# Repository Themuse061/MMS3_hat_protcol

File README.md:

# MMS3 Hat Protocol

## Sekcja 1: Dokumentacja Hat'a

### Krótki opis projektu
Moduł rozszerzeń protokołów komunikacyjnych dla standardu ChainBus. Hat umożliwia podłączanie urządzeń zewnętrznych komunikujących się za pomocą interfejsów UART, RS485, I2C oraz SPI.

Umożliwia  zmianę napięć logicznych (3.3V lub 5V) osobno dla każdej sekcji, a linie komunikacyjne są domyślnie odłączone przy starcie systemu.

### Zgodność ze standardem ChainBus

* ✅  Używa złącza ChainBus, nie zmienia jego miejsca ani pinoutu.
* ✅  Używa wyłącznie interfejsów I2C, SPI lub UART i nie inicjuje samodzielnie nowych transmisji (Nie jest master'em I2C albo SPI).
* ✅  Spełnia wymagania mechaniczne standardu (wymiary PCB, rozstaw otworów).
* ✅  Pobiera maksymalny prąd zgodny z ilością na jednego hat'a
* ✅  Obsługuje napięcie wejściowe BRD_VIN do wartości 48V.

### Komunikacja i adresowanie

#### Adresacja I2C
Do konfiguracji pracy buforów trójstanowych oraz transceiverów RS485 wykorzystywany jest ekspander GPIO.

| Układ (IC)     | Funkcja                              | Adres I2C (7-bit) |
| :------------- | :----------------------------------- | :---------------: |
| **TCA9535PWR** | Ekspander GPIO (sterowanie buforami) | `0100000b` (0x20) |

Uwaga: Adresy expander'a gpio i pamięci EEPROM są zajęte na I2C wychodzącym z hat'a

---

### Konfiguracja i wybór napięć logicznych (3.3V / 5V)

Sekcje UART1, UART2 oraz SPI posiadają niezależną regulację napięcia pracy za pomocą zworek:

| Zworka  | Sekcja | Pozycja 1-2              | Pozycja 2-3            |
| :------ | :----- | :----------------------- | :--------------------- |
| **J8**  | UART 1 | Napięcie logiki **3.3V** | Napięcie logiki **5V** |
| **J14** | UART 2 | Napięcie logiki **3.3V** | Napięcie logiki **5V** |
| **J5**  | SPI    | Napięcie logiki **3.3V** | Napięcie logiki **5V** |

---

### Pełny pinout ekspandera GPIO (TCA9535PWR)

Wszystkie magistrale (z wyjątkiem I2C) są przy starcie urządzenia **fizycznie odłączone**. Do ich aktywacji i konfiguracji służą poniższe piny ekspandera:

| Port    | Nazwa sygnału       | Domyślny stan sprzętowy  | Opis funkcjonalny                                              |
| :------ | :------------------ | :----------------------- | :------------------------------------------------------------- |
| **P00** | `UART 1 OE`         | Niski (L) - Odłączony    | Aktywacja (Output Enable) bufora linii UART 1                  |
| **P01** | `UART 1 RS485 RE_N` | Wysoki (H)  - Wyłączony  | Negowane wejście Receiver Enable ($\overline{RE}$) dla RS485-1 |
| **P02** | `UART 1 SHDN_N`     | Wysoki (H)   - Wyłączony | Negowane wejście Shutdown ($\overline{SD}$) dla RS485-1        |
| **P03** | `UART 1 BONUS OUT`  | Niski (L)                | Dodatkowe wyjście pomocnicze (Bonus Out) na złączu J12         |
| **P04** | `UART 1 BONUS OUT`  | Niski (L)                | Dodatkowe wyjście pomocnicze (Bonus Out) na złączu J12         |
| **P05** | `STATUS LED`        | -                        | Dioda statusowa ogólnego przeznaczenia (LED)                   |
| **P06** | `UART 2 OE`         | Niski (L) - Odłączony    | Aktywacja (Output Enable) bufora linii UART 2                  |
| **P07** | `UART 2 RS485 RE_N` | Wysoki (H) - Wyłączony   | Negowane wejście Receiver Enable ($\overline{RE}$) dla RS485-2 |
| **P10** | `UART 2 SHDN_N`     | Wysoki (H) - Wyłączony   | Negowane wejście Shutdown ($\overline{SD}$) dla RS485-2        |
| **P11** | `UART 2 BONUS OUT`  | Niski (L)                | Dodatkowe wyjście pomocnicze (Bonus Out) na złączu J13         |
| **P12** | `UART 2 BONUS OUT`  | Niski (L)                | Dodatkowe wyjście pomocnicze (Bonus Out) na złączu J13         |
| **P13** | `SPI 1 ENABLE`      | Niski (L) - Odłączony    | Aktywacja (Output Enable) bufora linii SPI                     |
| **P14** | `SPI 1 BONUS IN`    | —                        | Dodatkowe wejście pomocnicze (Bonus In) na złączu J9           |
| **P15** | `SPI 1 BONUS IN`    | —                        | Dodatkowe wejście pomocnicze (Bonus In) na złączu J9           |
| **P16** | `SPI 1 BONUS IN`    | —                        | Dodatkowe wejście pomocnicze (Bonus In) na złączu J9           |
| **P17** | `SPI 1 BONUS OUT`   | —                        | Dodatkowe wyjście pomocnicze (Bonus Out) na złączu J9          |

---

### Konfiguracja trybów pracy: UART vs RS485

Linie komunikacyjne oraz złącza fizyczne są współdzielone pomiędzy standardowym interfejsem UART a różnicowym RS485. Wymaga to odpowiedniej konfiguracji sprzętowej i programowej.

#### Tryb 1: Standardowy UART
Aby używać kanału jako klasycznego interfejsu UART:
1. **Włącz magistralę:** Ustaw odpowiedni pin `UART OE` (P00 lub P06) w stan wysoki (`1`).
2. **Wylutuj rezystor terminujący:** Należy  **odlutować rezystor terminujący RS485** ($120\ \Omega$) przypisany do danego kanału (rezystory są oznaczone  na  PCB). Pozostawienie rezystora obciąży linie RX/TX, co może powodować błędy lub uszkodzenie układu.

#### Tryb 2: Interfejs RS485
Aby używać kanału w standardzie  RS485:
1. **Włącz magistralę:** Ustaw odpowiedni pin `UART OE` (P00 lub P06) w stan wysoki (`1`).
2. **Aktywuj transceiver:** Ustaw piny Receiver Enable (`RE_N`) oraz Shutdown (`SHDN_N`) w stan niski (`0`).
3. **Terminacja linii:** Rezystor terminujący na PCB powinien pozostać wlutowany .

---

### Pinout złączy zewnętrznych

#### J11 (UART1 / RS485-1) oraz J15 (UART2 / RS485-2)
Złącza te współdzielą piny fizyczne dla obu standardów komunikacji.

| Pin   | Nazwa    | Funkcja w trybie UART         | Funkcja w trybie RS485                 |
| :---- | :------- | :---------------------------- | :------------------------------------- |
| **1** | `GND`    | Masa sygnałowa                | Masa odniesienia                       |
| **2** | `V_SEL`  | Wybrane zasilanie (3.3V / 5V) | Wybrane zasilanie (3.3V / 5V)          |
| **3** | `A / RX` | Odbiór danych (RX)            | Linia różnicowa **A** (nieodwracająca) |
| **4** | `B / TX` | Nadawanie danych (TX)         | Linia różnicowa **B** (odwracająca)    |

#### J4 (I2C 3.3V) oraz J6 (I2C 5V)
Złącza magistrali I2C są połączone na stałe do linii ChainBus poprzez odpowiednie translatory poziomów.
* **J4 (3.3V):** Pin 1: GND | Pin 2: 3.3V | Pin 3: SDA 3.3V | Pin 4: SCL 3.3V
* **J6 (5.0V):** Pin 1: GND | Pin 2: 5.0V | Pin 3: SDA 5.0V | Pin 4: SCL 5.0V

#### J7 (SPI)
Złącze magistrali SPI z konwersją napięć (3.3V / 5V w zależności od J5):
* Pin 1: GND | Pin 2: V_SEL | Pin 3: SCK | Pin 4: MOSI | Pin 5: MISO | Pin 6: CS

---

### Złącza pomocnicze (Bonus Pins)

Złącza te służą do wyprowadzenia dodatkowych sygnałów cyfrowych sprzężonych z buforami danej magistrali. Działają tylko wtedy, gdy bufor nadrzędnej magistrali jest włączony (`OE` = `1`).

* **J12 (UART 1):** Pin 1: `P01` (In) | Pin 2: `P02` (Out/In) | Pin 3: `P03` (Out) | Pin 4: `P04` (Out)
* **J13 (UART 2):** Pin 1: `P07` (In) | Pin 2: `P10` (Out/In) | Pin 3: `P11` (Out) | Pin 4: `P12` (Out)
* **J9 (SPI):** Pin 1: `P14` (In) | Pin 2: `P15` (In) | Pin 3: `P16` (In) | Pin 4: `P17` (Out)

---

### Gotowe arkusze hierarchiczne
W projekcie wykorzystano następujące arkusze hierarchiczne:
* **SPI tri state switch** – Moduł przełączania linii interfejsu SPI z użyciem buforów trójstanowych oraz układów konwersji poziomów napięciowych (3.3V <-> 5V).
* **UART tri state switch + RS485 converter** – Blok przełączania linii UART z dopasowaniem poziomów napięć oraz zintegrowanym transceiverem RS485 i układem sterowania przepływem danych (RE/SHDN).

---

## Sekcja 2: Specyfikacja standardu ChainBus

### Architektura i łączenie modułów
Standard ChainBus umożliwia modułowe łączenie hatów. Na jednym MMS3 można zamontować pionowo **do 8 hat'ów**. Połączenie realizowane jest poprzez wpięcie złącza męskiego kolejnego hat'a w złącze żeńskie poprzedniego.

### Komunikacja i sterowanie
Magistrala ChainBus jest w pełni cyfrowa. Płyta główna nie steruje bezpośrednio sygnałami ogólnego przeznaczenia (GPIO) na poszczególnych hat'ach. Wszelkie operacje (np. odczyt czujników, przełączanie magistral) muszą być realizowane przez dedykowane układy scalone komunikujące się przez interfejsy systemowe.

Wybór aktywnego modułu realizowany jest przez układ przełącznika magistrali (bus switch) na płycie głównej. Dzięki temu linie I2C, SPI i UART są niezależne dla każdego hat'a (brak konfliktów adresów I2C między różnymi hatami).
* **Identyfikacja:** Każdy moduł powinien posiadać pamięć EEPROM na magistrali I2C w celu identyfikacji płyty przez system - układ M24C64-W skonfigurowany na adres `1010000` przy liniach adresowych A0, A1, A2 zwartych do masy.

### Zasilanie
Złącze ChainBus dostarcza następujące linie zasilania:

| Magistrala zasilania | Napięcie znamionowe | Maksymalny prąd (łączny dla 8 hatów) | Szacowany prąd na jeden hat |
| :------------------- | :-----------------: | :----------------------------------: | :-------------------------: |
| **5V**               |        5.0 V        |                1.0 A                 |           125 mA            |
| **12V stby**         |       12.0 V        |                0.5 A                 |            65 mA            |
| **BRD_VIN**          |   12.0 V – 48.0 V   |                1.5 A                 |           185 mA            |

*   Komponenty podłączone do linii `BRD_VIN` muszą być przystosowane do pracy z napięciem od 12V do **48 V**.

### Wymagania mechaniczne i złącza
* **Wymiary PCB:** Niedozwolona jest zmiana obrysu płytki oraz położenia otworów montażowych, aby zachować kompatybilność mechaniczną.
* **Pozycjonowanie złączy ChainBus:** Położenie złącza standardu 2x16 SMD (raster 2.54 mm) musi być zgodne z szablonem. Złącze żeńskie montowane jest na stronie FRONT, natomiast złącze męskie na stronie BACK.
* **Komponenty:** Wszystkie komponenty powinny znajdować się na stronie FRONT płytki, aby uniknąć kolizji mechanicznych z elementami sąsiadujących modułów w stosie.

---

## Sekcja 3: Licencje

### Licencje projektu

*   **PCB:** CERN-OHL-P
*   **Software:** MIT License

[Template](https://github.com/KoNaR-Hefajstos/MMS3_hat_templates/) jest na licencji CC0 1.0 Universal. **Reszta projektu nie jest na tej licencji**

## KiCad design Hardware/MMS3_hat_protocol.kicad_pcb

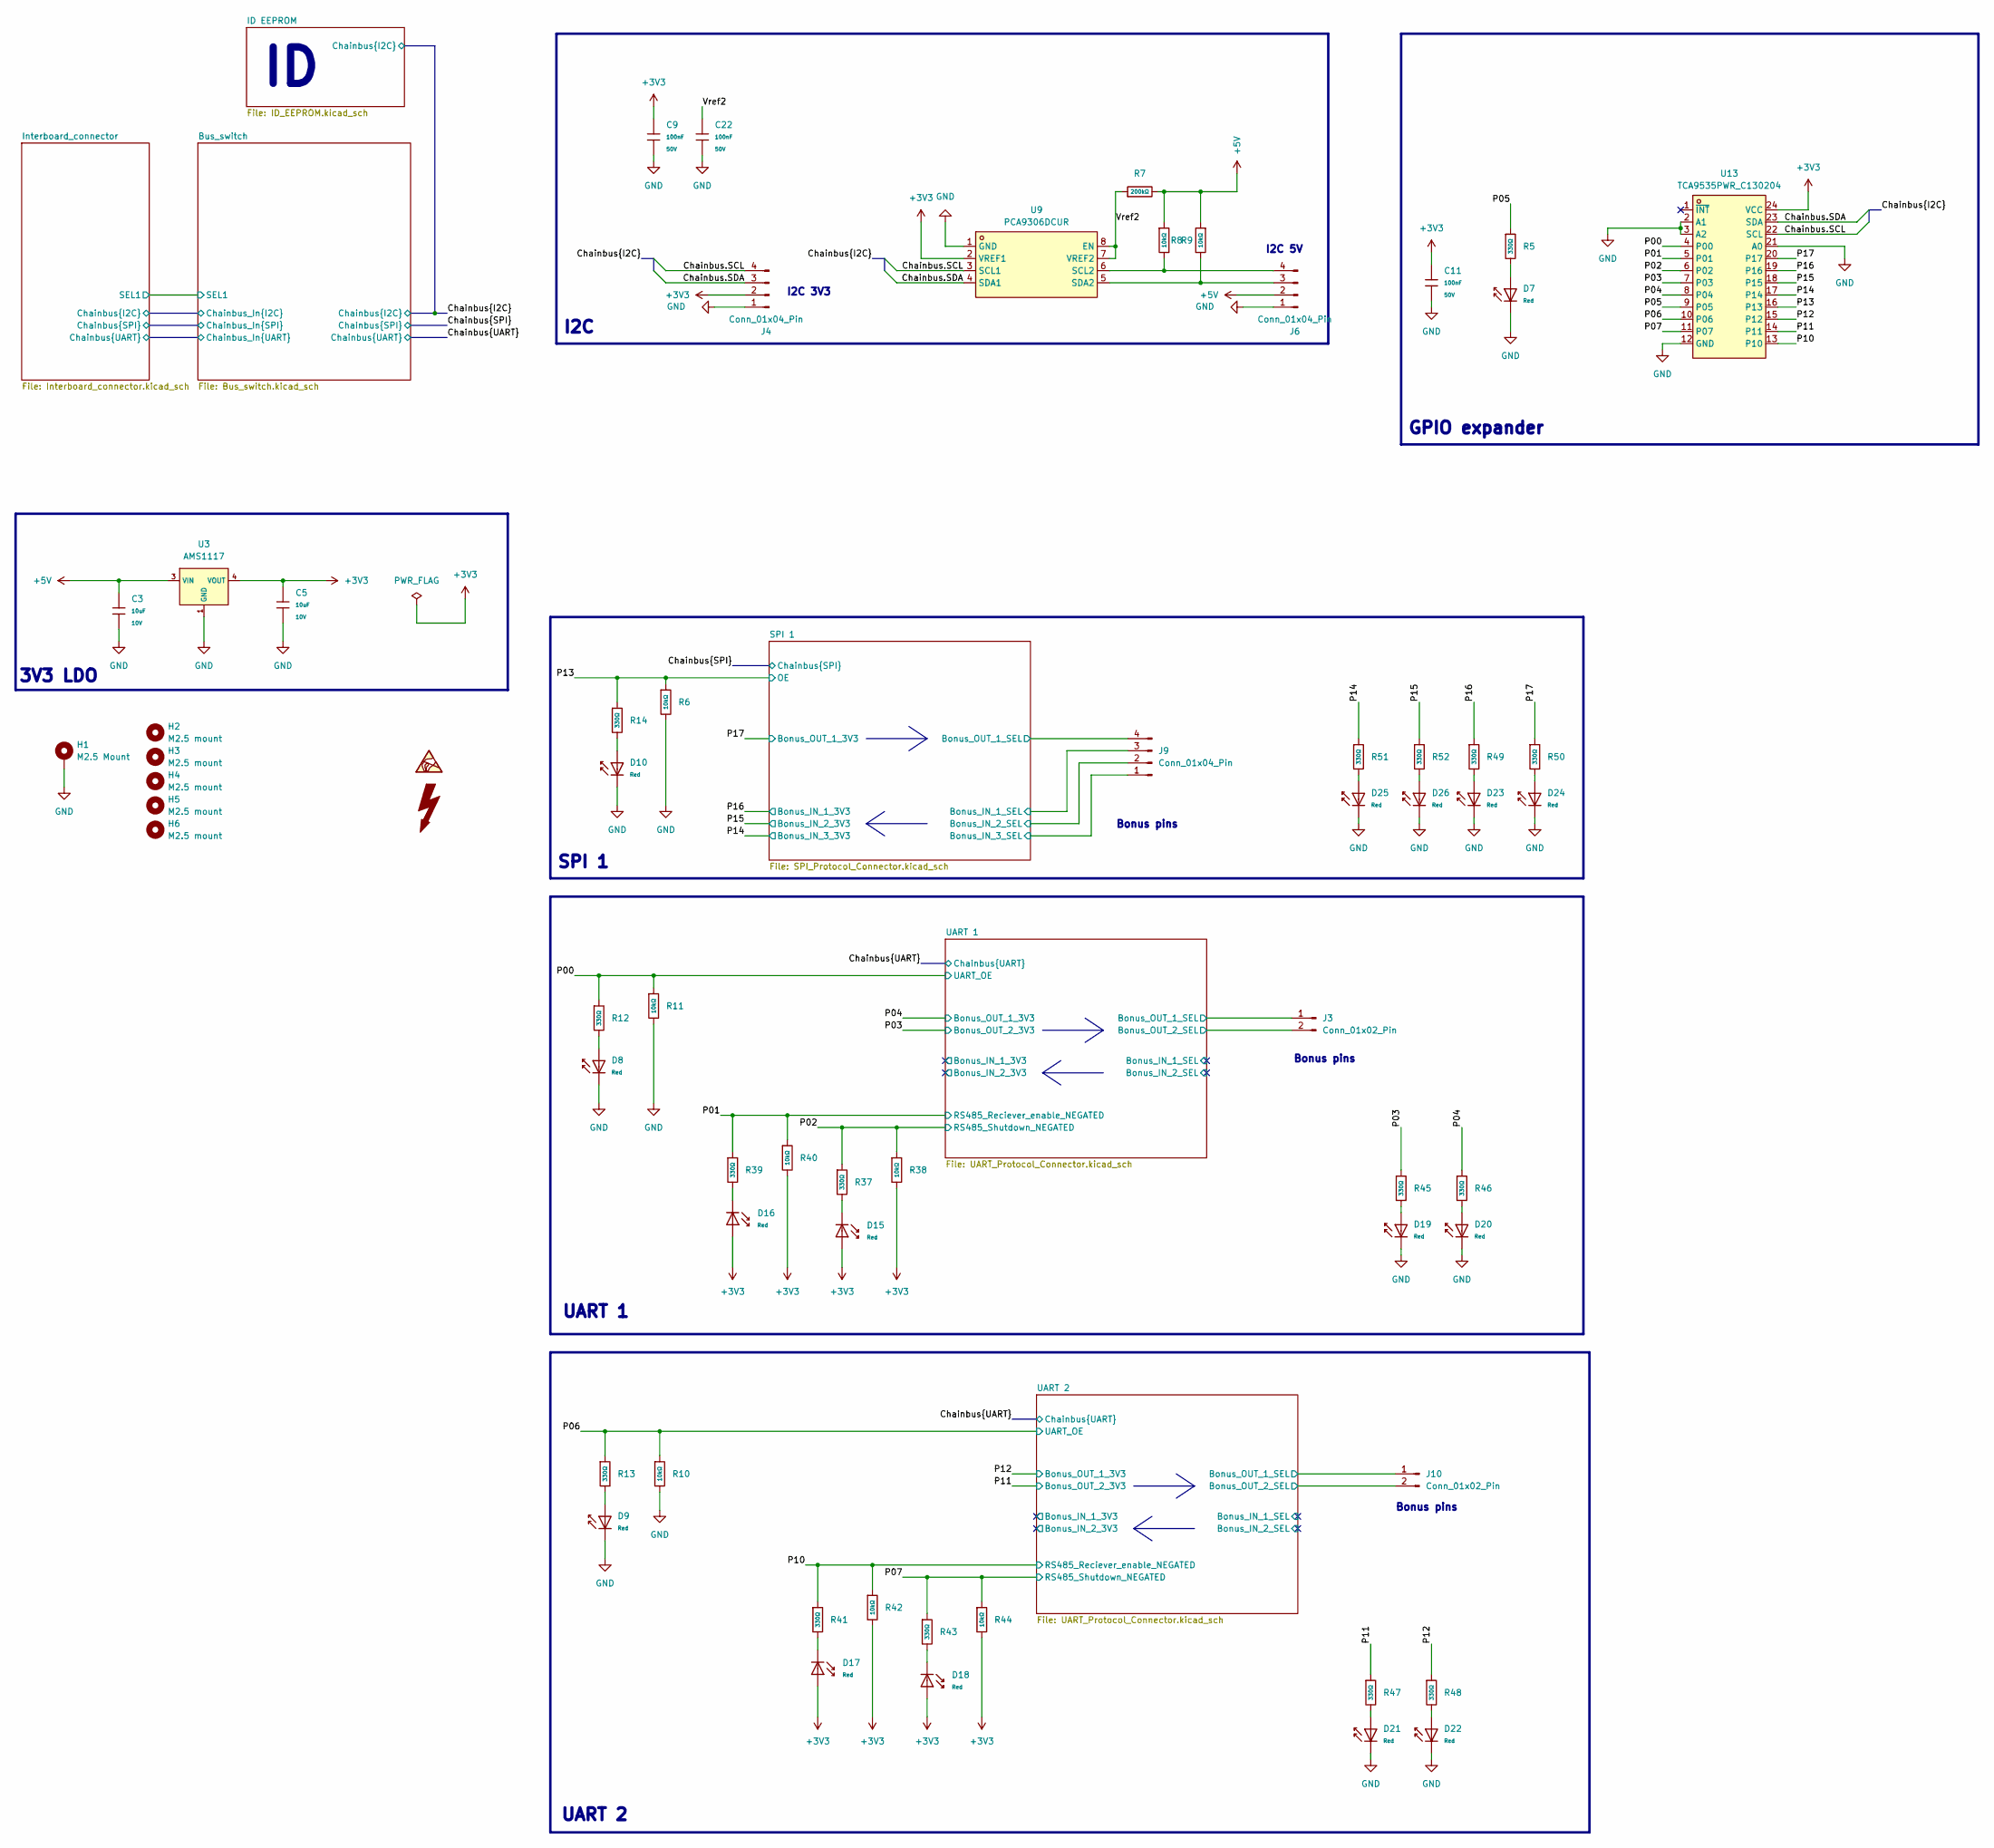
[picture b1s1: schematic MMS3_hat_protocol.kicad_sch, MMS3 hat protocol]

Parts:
C3, C5: 10uF; C_0603; Voltage Rated 10V; Tolerance ±10%; Part CL10A106KP8NNNC; LCSC C19702
C9, C11, C22: 100nF; C_0603; Voltage Rated 50V; Tolerance ±10%; Part CC0603KRX7R9BB104; LCSC C14663
D7, D8, D9, D10, D15, D16, D17, D18, D19, D20, D21, D22, D23, D24, D25, D26: Red; D_0603; Part KT-0603R; LCSC C2286
H1: M2.5 Mount; MountingHole_2.7mm_M2.5_DIN965_Pad_TopOnly
H2, H3, H4, H5, H6: M2.5 mount; MountingHole_2.7mm_M2.5
J3, J10: Conn_01x02_Pin; PinSocket_1x02_P2.54mm_Vertical
J4, J6: Conn_01x04_Pin; JST_XH_S4B-XH-A_1x04_P2.50mm_Horizontal
J9: Conn_01x04_Pin; PinSocket_1x04_P2.54mm_Vertical
R5, R12, R13, R14, R37, R39, R41, R43, R45, R46, R47, R48, R49, R50, R51, R52: 330Ω; R_0402; Overload Voltage (Max) 50V; Tolerance ±1%; Part 0402WGF3300TCE; LCSC C25104
R6, R8, R9, R10, R11, R38, R40, R42, R44: 10kΩ; R_0402; Overload Voltage (Max) 50V; Tolerance ±1%; Part 0402WGF1002TCE; LCSC C25744
R7: 200kΩ; R_0402; Overload Voltage (Max) 50V; Tolerance ±1%; Part 0402WGF2003TCE; LCSC C25764
U3: AMS1117; SOT-223-3_L6.5-W3.4-P2.30-LS7.0-BR; Output Voltage 3.3V; Dropout Voltage 1.3V@(800mA); Part AMS1117-3.3; LCSC C6186
U9: PCA9306DCUR; SSOP-8_L2.0-W2.3-P0.50-LS3.1-BR; MPN PCA9306DCUR; LCSC Part C33196
U13: TCA9535PWR_C130204; TSSOP-24_L7.8-W4.4-P0.65-LS6.4-BL; MPN TCA9535PWR; LCSC Part C130204

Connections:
+3V3: C5.1, C9.1, C11.1, D15.2, D16.2, D17.2, D18.2, J4.2, R38.2, R40.2, R42.2, R44.2, U3.2 (VOUT), U3.4 (VOUT), U9.2 (VREF1), U13.24 (VCC); also elsewhere on the board
+5V: C3.1, J6.2, R7.2, R8.1, R9.1, U3.3 (VIN); also elsewhere on the board
/Chainbus.SCL: J4.4, U9.3 (SCL1), U13.22 (SCL); also elsewhere on the board
/Chainbus.SDA: J4.3, U9.4 (SDA1), U13.23 (SDA); also elsewhere on the board
/P00: R11.1, R12.1, U13.4 (P00); also elsewhere on the board
/P01: R39.1, R40.1, U13.5 (P01); also elsewhere on the board
/P02: R37.1, R38.1, U13.6 (P02); also elsewhere on the board
/P03: R45.1, U13.7 (P03); also elsewhere on the board
/P04: R46.1, U13.8 (P04); also elsewhere on the board
/P05: R5.1, U13.9 (P05)
/P06: R10.1, R13.1, U13.10 (P06); also elsewhere on the board
/P07: R43.1, R44.1, U13.11 (P07); also elsewhere on the board
/P10: R41.1, R42.1, U13.13 (P10); also elsewhere on the board
/P11: R47.1, U13.14 (P11); also elsewhere on the board
/P12: R48.1, U13.15 (P12); also elsewhere on the board
/P13: R6.1, R14.1, U13.16 (P13); also elsewhere on the board
/P14: R51.1, U13.17 (P14); also elsewhere on the board
/P15: R52.1, U13.18 (P15); also elsewhere on the board
/P16: R49.1, U13.19 (P16); also elsewhere on the board
/P17: R50.1, U13.20 (P17); also elsewhere on the board
/SPI 1/Bonus_IN_1_SEL: J9.3; also elsewhere on the board
/SPI 1/Bonus_IN_2_SEL: J9.2; also elsewhere on the board
/SPI 1/Bonus_IN_3_SEL: J9.1; also elsewhere on the board
/SPI 1/Bonus_OUT_1_SEL: J9.4; also elsewhere on the board
/UART 1/Bonus_OUT_1_SEL: J3.1; also elsewhere on the board
/UART 1/Bonus_OUT_2_SEL: J3.2; also elsewhere on the board
/UART 2/Bonus_OUT_1_SEL: J10.1; also elsewhere on the board
/UART 2/Bonus_OUT_2_SEL: J10.2; also elsewhere on the board
/Vref2: C22.1, R7.1, U9.7 (VREF2), U9.8 (EN)
GND: C3.2, C5.2, C9.2, C11.2, C22.2, D7.1, D8.1, D9.1, D10.1, D19.1, D20.1, D21.1, D22.1, D23.1, D24.1, D25.1, D26.1, H1.1 (1_1), J4.1, J6.1, R6.2, R10.2, R11.2, U3.1 (GND), U9.1 (GND), U13.2 (A1), U13.3 (A2), U13.12 (GND), U13.21 (A0); also elsewhere on the board
unnamed: D7.2, R5.2
unnamed: D8.2, R12.2
unnamed: D9.2, R13.2
unnamed: D10.2, R14.2
unnamed: D15.1, R37.2
unnamed: D16.1, R39.2
unnamed: D17.1, R41.2
unnamed: D18.1, R43.2
unnamed: D19.2, R45.2
unnamed: D20.2, R46.2
unnamed: D21.2, R47.2
unnamed: D22.2, R48.2
unnamed: D23.2, R49.2
unnamed: D24.2, R50.2
unnamed: D25.2, R51.2
unnamed: D26.2, R52.2
unnamed: J6.3, R9.2, U9.5 (SDA2)
unnamed: J6.4, R8.2, U9.6 (SCL2)

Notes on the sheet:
I2C 3V3
GPIO expander
Bonus pins
UART 1
I2C 5V
3V3 LDO
I2C
SPI 1
UART 2

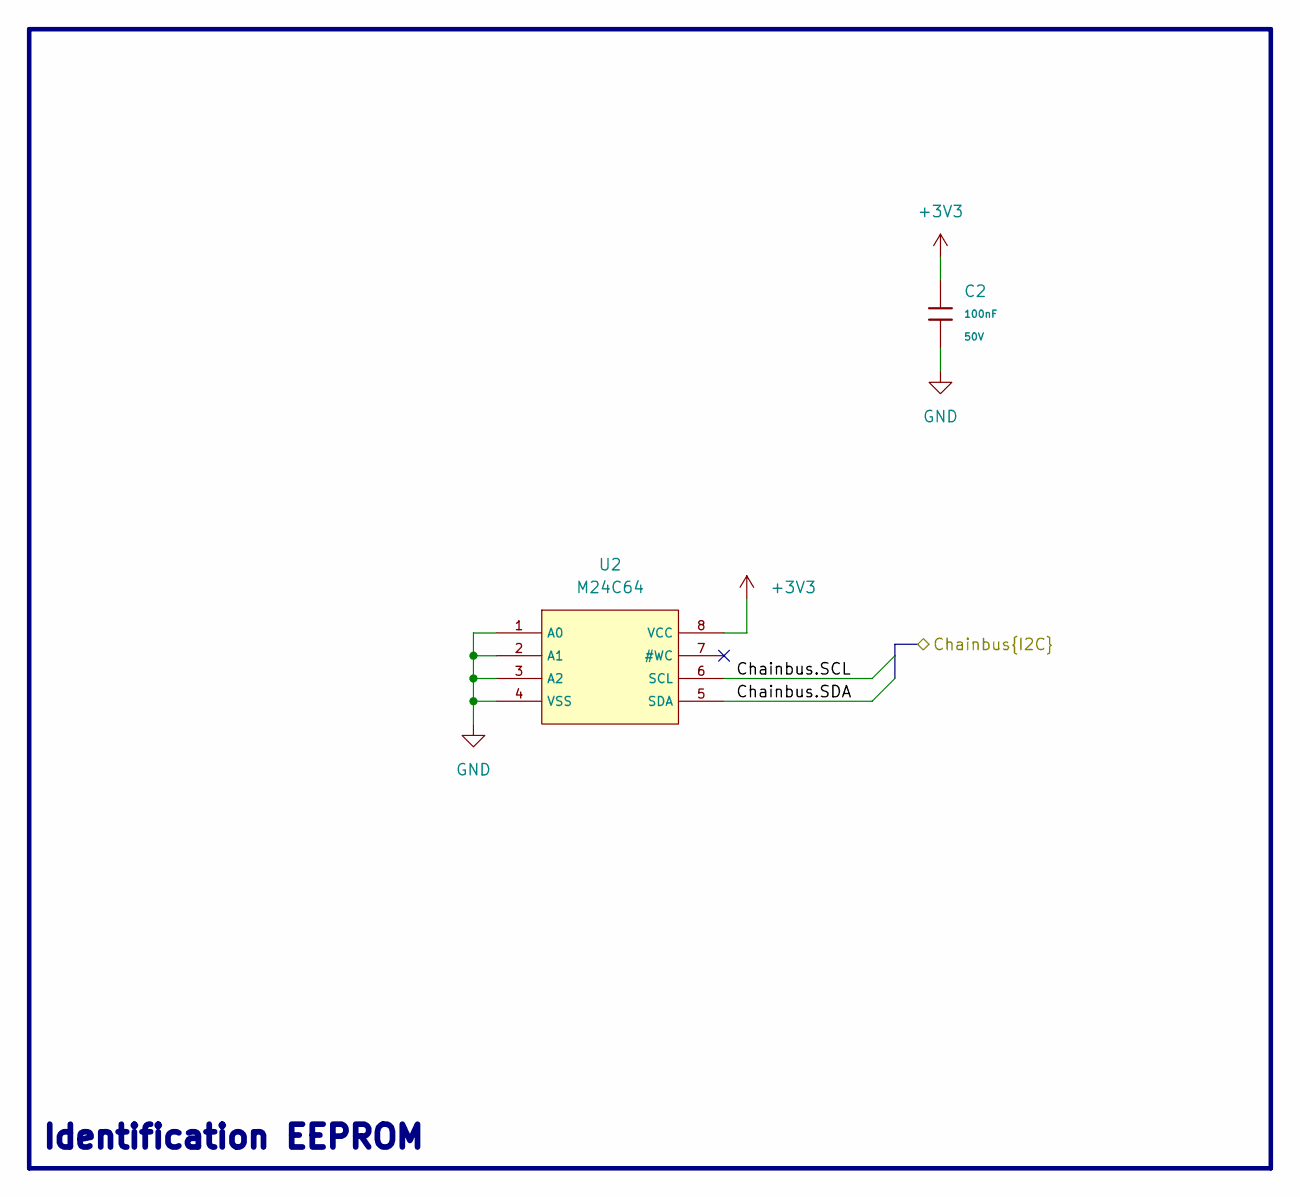
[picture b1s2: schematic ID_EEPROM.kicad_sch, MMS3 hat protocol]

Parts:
C2: 100nF; C_0603; Voltage Rated 50V; Tolerance ±10%; Part CC0603KRX7R9BB104; LCSC C14663
U2: M24C64; SOIC-8_L5.0-W4.0-P1.27-LS6.0-BL; Supply Voltage 1.8V~5.5V; Part M24C64-RMN6TP; LCSC C79988

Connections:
+3V3: C2.1, U2.8 (VCC); also elsewhere on the board
/Chainbus.SCL: U2.6 (SCL); also elsewhere on the board
/Chainbus.SDA: U2.5 (SDA); also elsewhere on the board
GND: C2.2, U2.1 (A0), U2.2 (A1), U2.3 (A2), U2.4 (VSS); also elsewhere on the board

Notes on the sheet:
Identification EEPROM

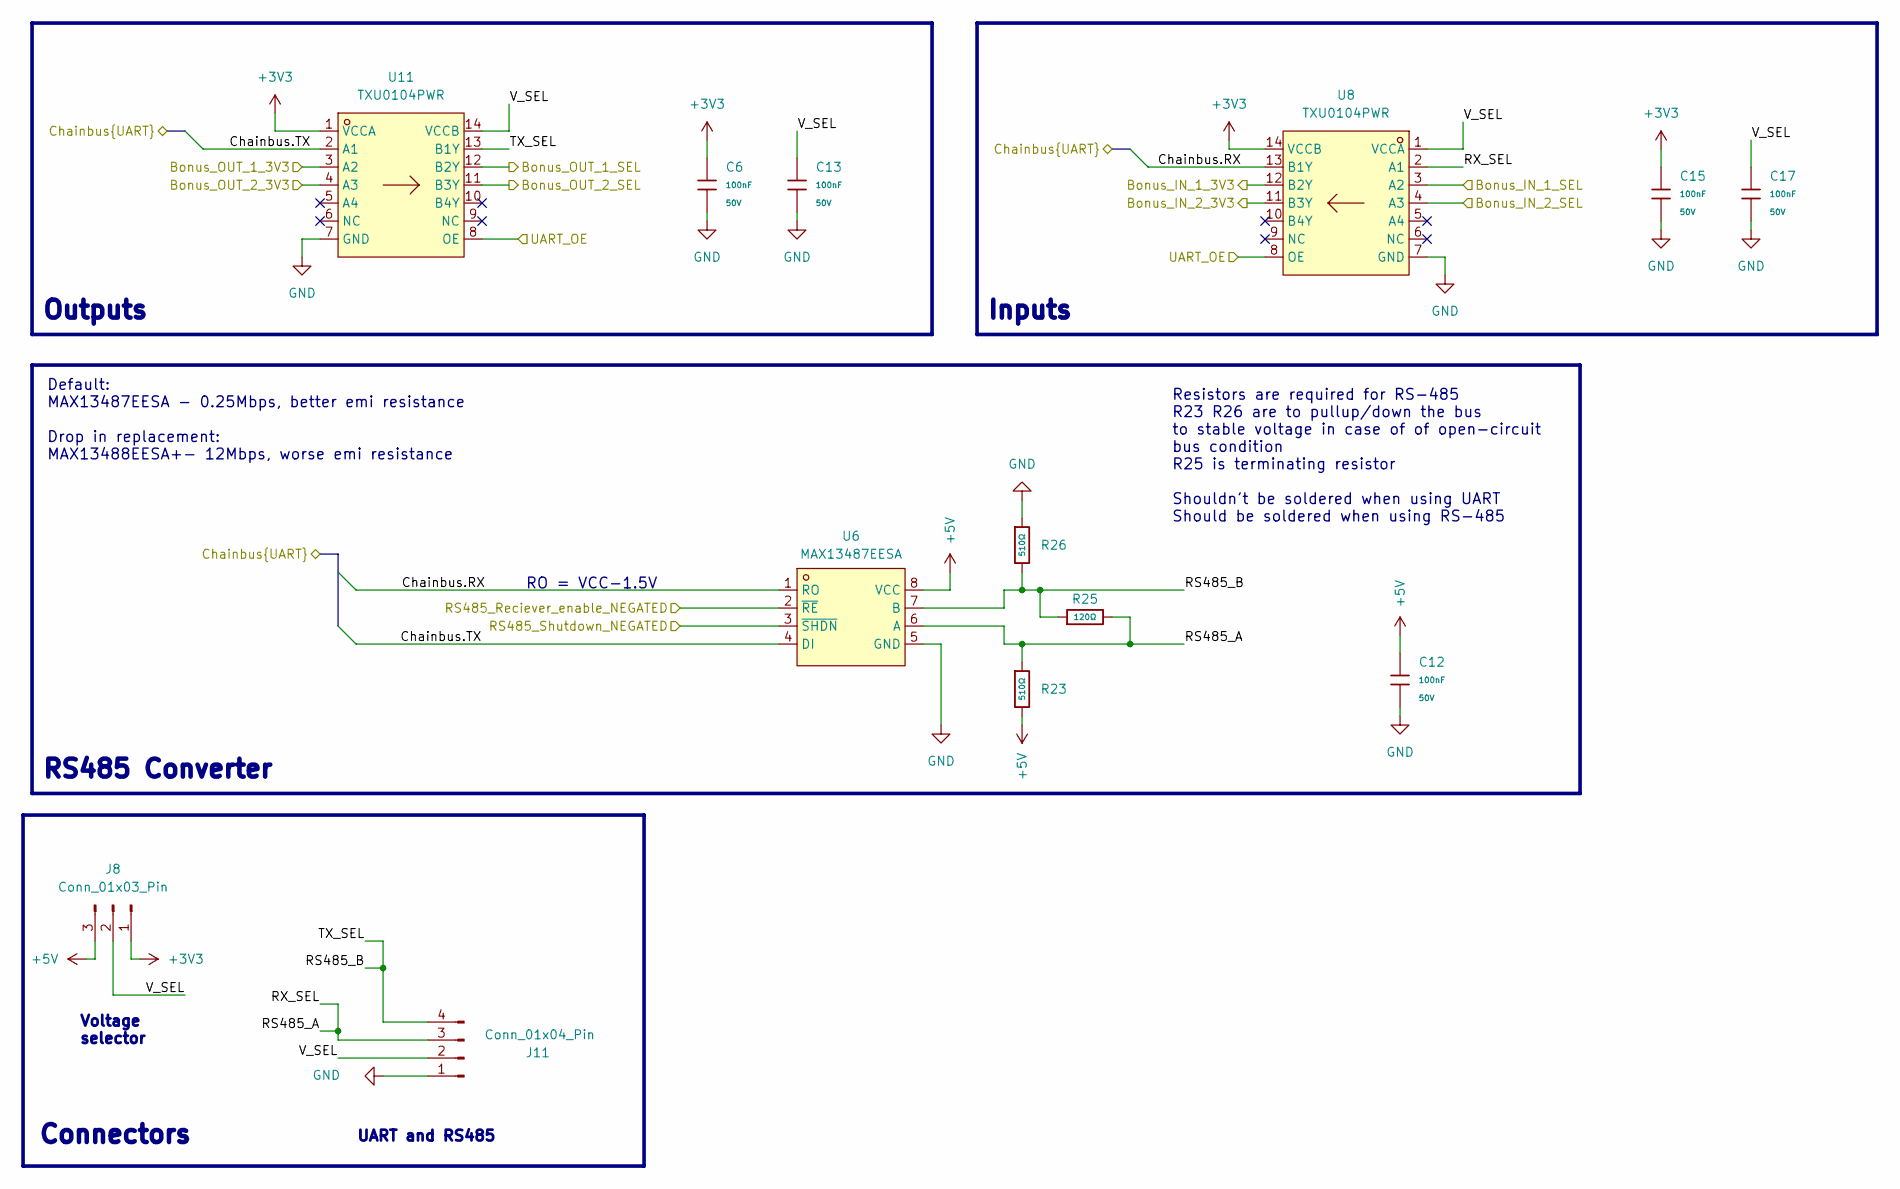
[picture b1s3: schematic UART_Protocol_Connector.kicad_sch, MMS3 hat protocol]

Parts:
C6, C12, C13, C15, C17: 100nF; C_0603; Voltage Rated 50V; Tolerance ±10%; Part CC0603KRX7R9BB104; LCSC C14663
J8: Conn_01x03_Pin; PinSocket_1x03_P2.54mm_Horizontal
J11: Conn_01x04_Pin; JST_XH_S4B-XH-A_1x04_P2.50mm_Horizontal
R23, R26: 510Ω; R_0603; Overload Voltage (Max) 75V; Tolerance ±1%; Part 0603WAF5100T5E; LCSC C23193
R25: 120Ω; R_0603; Overload Voltage (Max) 75V; Tolerance ±1%; Part 0603WAF1200T5E; LCSC C22787
U6: MAX13487EESA; SOIC-8_L4.9-W3.9-P1.27-LS6.0-BL; MPN MAX13487EESA+T; LCSC Part C18347
U8, U11: TXU0104PWR; TSSOP-14_L5.0-W4.4-P0.65-LS6.4-BL; LCSC Part C2938871

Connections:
+3V3: C6.1, C15.1, J8.1, U8.14 (VCCB), U11.1 (VCCA); also elsewhere on the board
+5V: C12.1, J8.3, R23.2, U6.8 (VCC); also elsewhere on the board
/Chainbus.RX: U6.1 (RO), U8.13 (B1Y); also elsewhere on the board
/Chainbus.TX: U6.4 (DI), U11.2 (A1); also elsewhere on the board
/P00: U8.8 (OE), U11.8 (OE); also elsewhere on the board
/P01: U6.2 (~RE); also elsewhere on the board
/P02: U6.3 (~SHDN); also elsewhere on the board
/P03: U11.4 (A3); also elsewhere on the board
/P04: U11.3 (A2); also elsewhere on the board
/UART 1/Bonus_IN_1_3V3: U8.12 (B2Y)
/UART 1/Bonus_IN_1_SEL: U8.3 (A2)
/UART 1/Bonus_IN_2_3V3: U8.11 (B3Y)
/UART 1/Bonus_IN_2_SEL: U8.4 (A3)
/UART 1/Bonus_OUT_1_SEL: U11.12 (B2Y); also elsewhere on the board
/UART 1/Bonus_OUT_2_SEL: U11.11 (B3Y); also elsewhere on the board
/UART 1/RS485_A: J11.3, R23.1, R25.2, U6.6 (A), U8.2 (A1)
/UART 1/RS485_B: J11.4, R25.1, R26.2, U6.7 (B), U11.13 (B1Y)
/UART 1/V_SEL: C13.1, C17.1, J8.2, J11.2, U8.1 (VCCA), U11.14 (VCCB)
GND: C6.2, C12.2, C13.2, C15.2, C17.2, J11.1, R26.1, U6.5 (GND), U8.7 (GND), U11.7 (GND); also elsewhere on the board

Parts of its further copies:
C14, C18, C19, C20, C21: 100nF; C_0603; Voltage Rated 50V; Tolerance ±10%; Part CC0603KRX7R9BB104; LCSC C14663
J14: Conn_01x03_Pin; PinSocket_1x03_P2.54mm_Horizontal
J15: Conn_01x04_Pin; JST_XH_S4B-XH-A_1x04_P2.50mm_Horizontal
R24, R27: 510Ω; R_0603; Overload Voltage (Max) 75V; Tolerance ±1%; Part 0603WAF5100T5E; LCSC C23193
R28: 120Ω; R_0603; Overload Voltage (Max) 75V; Tolerance ±1%; Part 0603WAF1200T5E; LCSC C22787
U10, U12: TXU0104PWR; TSSOP-14_L5.0-W4.4-P0.65-LS6.4-BL; LCSC Part C2938871
U15: MAX13487EESA; SOIC-8_L4.9-W3.9-P1.27-LS6.0-BL; MPN MAX13487EESA+T; LCSC Part C18347

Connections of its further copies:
+3V3: C18.1, C20.1, J14.1, U10.1 (VCCA), U12.14 (VCCB); also elsewhere on the board
+5V: C14.1, J14.3, R24.2, U15.8 (VCC); also elsewhere on the board
/Chainbus.RX: U12.13 (B1Y), U15.1 (RO); also elsewhere on the board
/Chainbus.TX: U10.2 (A1), U15.4 (DI); also elsewhere on the board
/P06: U10.8 (OE), U12.8 (OE); also elsewhere on the board
/P07: U15.3 (~SHDN); also elsewhere on the board
/P10: U15.2 (~RE); also elsewhere on the board
/P11: U10.4 (A3); also elsewhere on the board
/P12: U10.3 (A2); also elsewhere on the board
/UART 2/Bonus_IN_1_3V3: U12.12 (B2Y)
/UART 2/Bonus_IN_1_SEL: U12.3 (A2)
/UART 2/Bonus_IN_2_3V3: U12.11 (B3Y)
/UART 2/Bonus_IN_2_SEL: U12.4 (A3)
/UART 2/Bonus_OUT_1_SEL: U10.12 (B2Y); also elsewhere on the board
/UART 2/Bonus_OUT_2_SEL: U10.11 (B3Y); also elsewhere on the board
/UART 2/RS485_A: J15.3, R24.1, R28.2, U12.2 (A1), U15.6 (A)
/UART 2/RS485_B: J15.4, R27.2, R28.1, U10.13 (B1Y), U15.7 (B)
/UART 2/V_SEL: C19.1, C21.1, J14.2, J15.2, U10.14 (VCCB), U12.1 (VCCA)
GND: C14.2, C18.2, C19.2, C20.2, C21.2, J15.1, R27.1, U10.7 (GND), U12.7 (GND), U15.5 (GND); also elsewhere on the board

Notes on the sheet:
Connectors
Voltage selector
UART and RS485
Default: MAX13487EESA - 0.25Mbps, better emi resistance Drop in replacement: MAX13488EESA+- 12Mbps, worse emi resistance
Inputs
RO = VCC-1.5V
Resistors are required for RS-485 R23 R26 are to pullup/down the bus to stable voltage in case of of open-circuit bus condition R25 is terminating resistor Shouldn't be soldered when using UART Should be soldered when using RS-485
RS485 Converter
Outputs

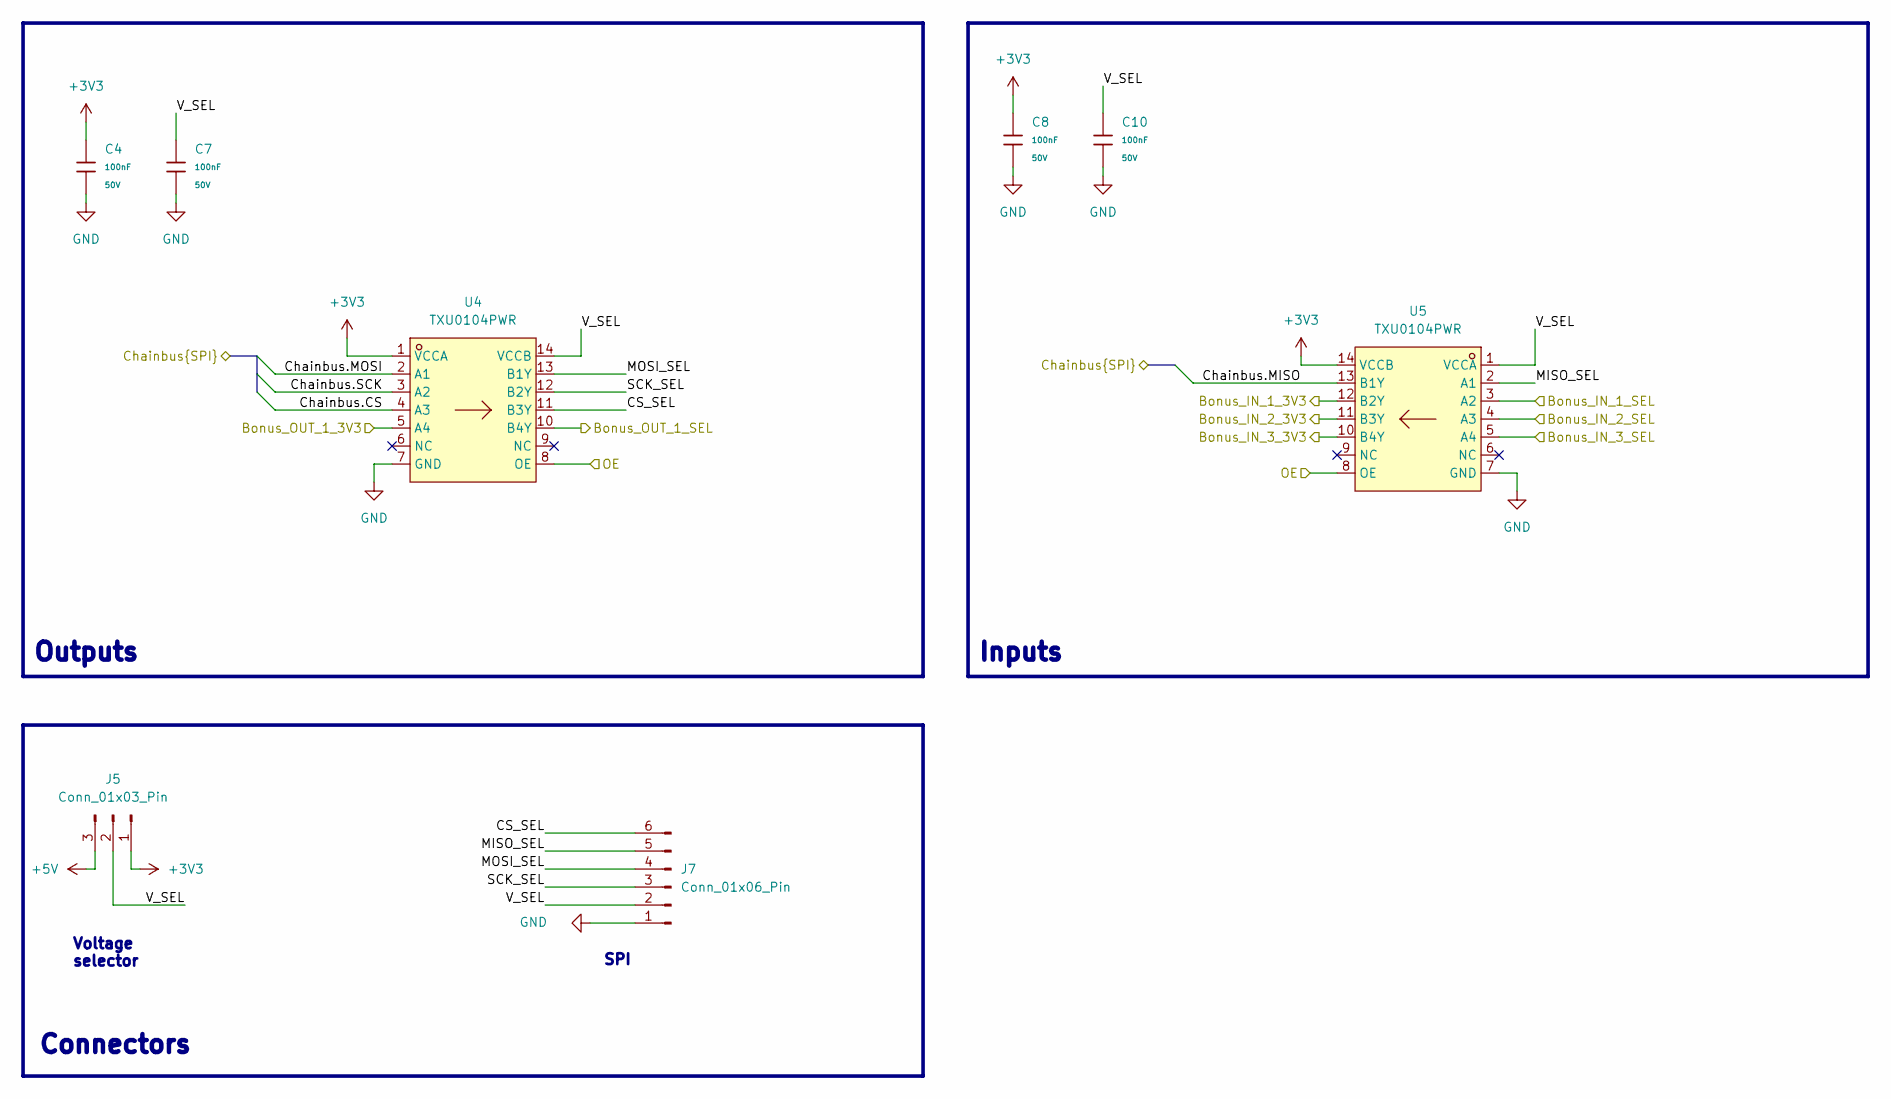
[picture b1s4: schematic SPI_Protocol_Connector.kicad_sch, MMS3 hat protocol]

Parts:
C4, C7, C8, C10: 100nF; C_0603; Voltage Rated 50V; Tolerance ±10%; Part CC0603KRX7R9BB104; LCSC C14663
J5: Conn_01x03_Pin; PinSocket_1x03_P2.54mm_Horizontal
J7: Conn_01x06_Pin; JST_XH_S6B-XH-A_1x06_P2.50mm_Horizontal
U4, U5: TXU0104PWR; TSSOP-14_L5.0-W4.4-P0.65-LS6.4-BL; LCSC Part C2938871

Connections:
+3V3: C4.1, C8.1, J5.1, U4.1 (VCCA), U5.14 (VCCB); also elsewhere on the board
+5V: J5.3; also elsewhere on the board
/Chainbus.CS: U4.4 (A3); also elsewhere on the board
/Chainbus.MISO: U5.13 (B1Y); also elsewhere on the board
/Chainbus.MOSI: U4.2 (A1); also elsewhere on the board
/Chainbus.SCK: U4.3 (A2); also elsewhere on the board
/P13: U4.8 (OE), U5.8 (OE); also elsewhere on the board
/P14: U5.10 (B4Y); also elsewhere on the board
/P15: U5.11 (B3Y); also elsewhere on the board
/P16: U5.12 (B2Y); also elsewhere on the board
/P17: U4.5 (A4); also elsewhere on the board
/SPI 1/Bonus_IN_1_SEL: U5.3 (A2); also elsewhere on the board
/SPI 1/Bonus_IN_2_SEL: U5.4 (A3); also elsewhere on the board
/SPI 1/Bonus_IN_3_SEL: U5.5 (A4); also elsewhere on the board
/SPI 1/Bonus_OUT_1_SEL: U4.10 (B4Y); also elsewhere on the board
/SPI 1/CS_SEL: J7.6, U4.11 (B3Y)
/SPI 1/MISO_SEL: J7.5, U5.2 (A1)
/SPI 1/MOSI_SEL: J7.4, U4.13 (B1Y)
/SPI 1/SCK_SEL: J7.3, U4.12 (B2Y)
/SPI 1/V_SEL: C7.1, C10.1, J5.2, J7.2, U4.14 (VCCB), U5.1 (VCCA)
GND: C4.2, C7.2, C8.2, C10.2, J7.1, U4.7 (GND), U5.7 (GND); also elsewhere on the board

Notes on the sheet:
Inputs
SPI
Connectors
Outputs
Voltage selector

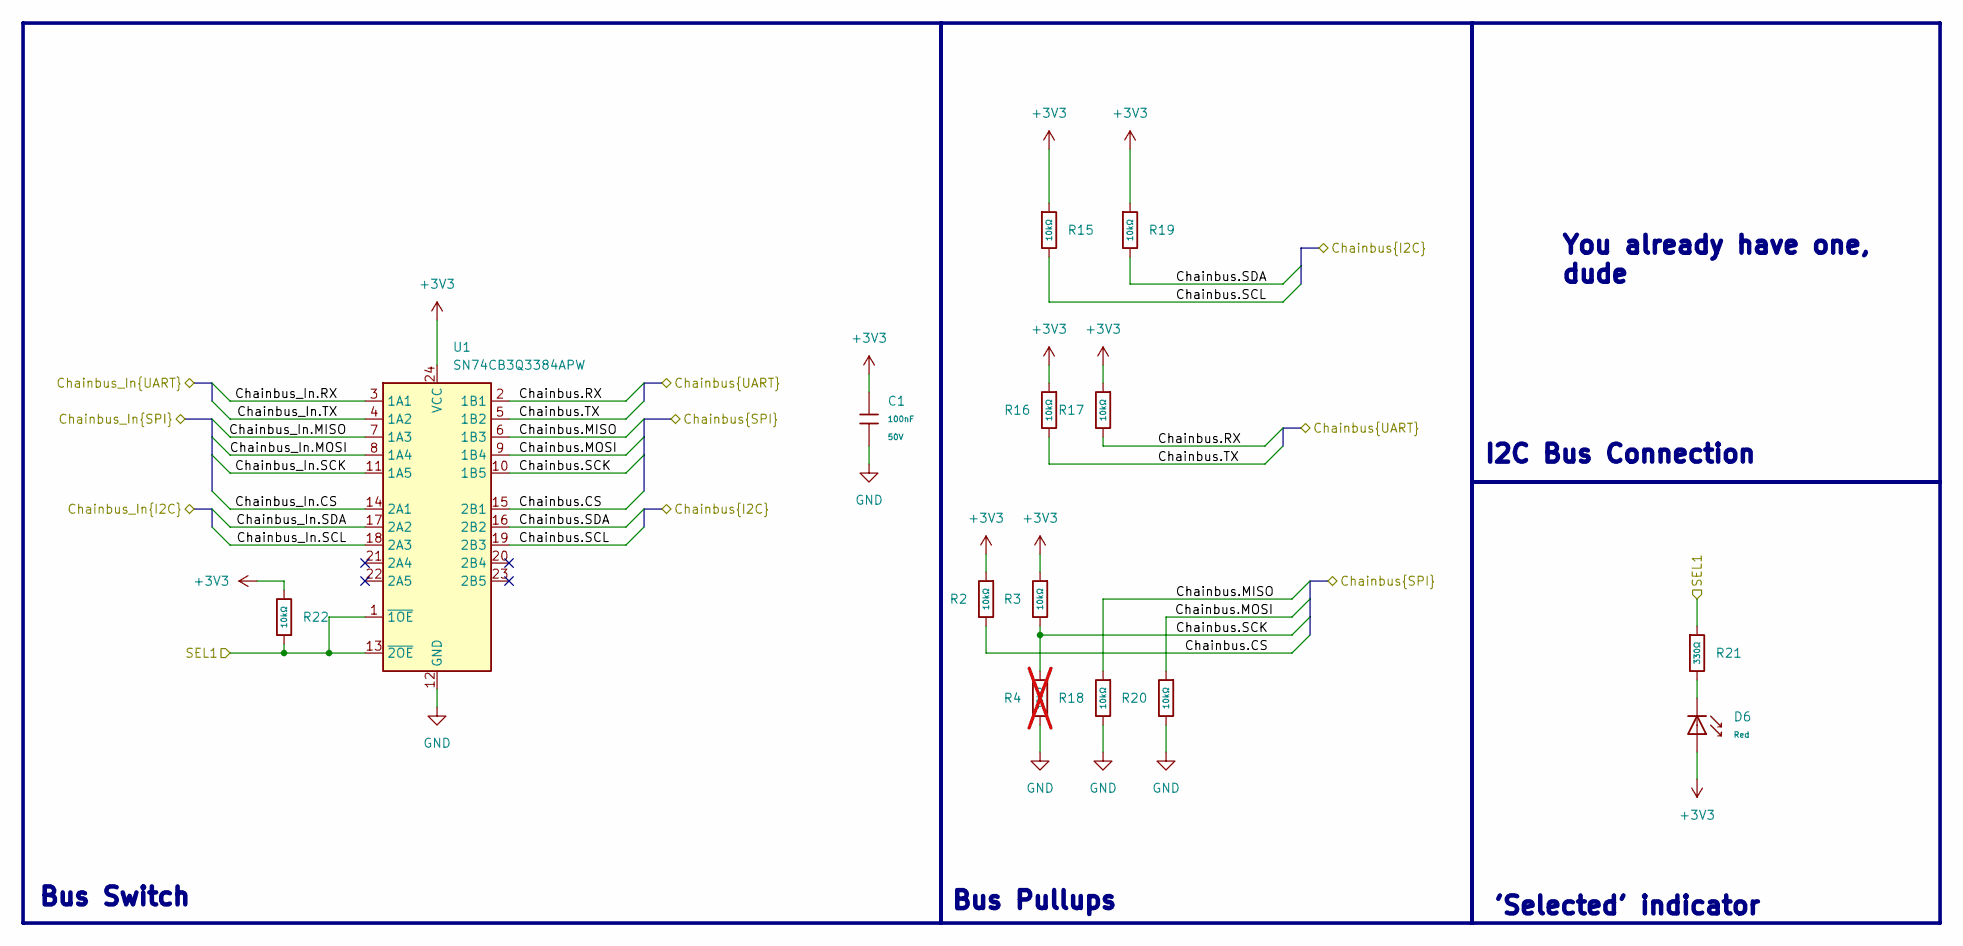
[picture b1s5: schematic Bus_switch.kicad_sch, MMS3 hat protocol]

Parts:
C1: 100nF; C_0603; Voltage Rated 50V; Tolerance ±10%; Part CC0603KRX7R9BB104; LCSC C14663
D6: Red; D_0603; Part KT-0603R; LCSC C2286
R2, R3, R15, R16, R17, R18, R19, R20, R22: 10kΩ; R_0402; Overload Voltage (Max) 50V; Tolerance ±1%; Part 0402WGF1002TCE; LCSC C25744
R4: 10kΩ; R_0402; Overload Voltage (Max) 50V; Tolerance ±1%; Part 0402WGF1002TCE; LCSC C25744; not fitted
R21: 330Ω; R_0402; Overload Voltage (Max) 50V; Tolerance ±1%; Part 0402WGF3300TCE; LCSC C25104
U1: SN74CB3Q3384APW; TSSOP-24_4.4x7.8mm_P0.65mm; LCSC C469874

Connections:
+3V3: C1.1, D6.2, R2.1, R3.1, R15.1, R16.1, R17.1, R19.1, R22.2, U1.24 (VCC); also elsewhere on the board
/Bus_switch/Chainbus_In.CS: U1.14 (2A1); also elsewhere on the board
/Bus_switch/Chainbus_In.MISO: U1.7 (1A3); also elsewhere on the board
/Bus_switch/Chainbus_In.MOSI: U1.8 (1A4); also elsewhere on the board
/Bus_switch/Chainbus_In.RX: U1.3 (1A1); also elsewhere on the board
/Bus_switch/Chainbus_In.SCK: U1.11 (1A5); also elsewhere on the board
/Bus_switch/Chainbus_In.SCL: U1.18 (2A3); also elsewhere on the board
/Bus_switch/Chainbus_In.SDA: U1.17 (2A2); also elsewhere on the board
/Bus_switch/Chainbus_In.TX: U1.4 (1A2); also elsewhere on the board
/Bus_switch/SEL1: R21.1, R22.1, U1.1 (~1OE), U1.13 (~2OE); also elsewhere on the board
/Chainbus.CS: R2.2, U1.15 (2B1); also elsewhere on the board
/Chainbus.MISO: R18.1, U1.6 (1B3); also elsewhere on the board
/Chainbus.MOSI: R20.1, U1.9 (1B4); also elsewhere on the board
/Chainbus.RX: R17.2, U1.2 (1B1); also elsewhere on the board
/Chainbus.SCK: R3.2, R4.1, U1.10 (1B5); also elsewhere on the board
/Chainbus.SCL: R15.2, U1.19 (2B3); also elsewhere on the board
/Chainbus.SDA: R19.2, U1.16 (2B2); also elsewhere on the board
/Chainbus.TX: R16.2, U1.5 (1B2); also elsewhere on the board
GND: C1.2, R4.2, R18.2, R20.2, U1.12 (GND); also elsewhere on the board
unnamed: D6.1, R21.2

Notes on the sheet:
Bus Switch
Bus Pullups
You already have one, dude
'Selected' indicator
I2C Bus Connection
